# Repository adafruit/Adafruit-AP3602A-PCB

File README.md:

## Adafruit MiniBoost 5V @ 100mA Charge Pump - AP3602A PCB

<a href="http://www.adafruit.com/products/3661"><br/>
Click here to purchase one from the Adafruit shop</a>

PCB files for the Adafruit MiniBoost 5V @ 100mA Charge Pump - AP3602A.

Format is EagleCAD schematic and board layout
* https://www.adafruit.com/product/3661

### Description

This adorable little board will come in very handy whenever you need a small amount of 5V power. It's the size of a linear regulator, but it's actually a mini-booster! Input 3V on one side, and get 5V at up to 100mA supply on the other. Perfect for use with battery-powered projects with 2 or 3 Alkaline, or a single Lithium battery. For big projects, you may want one of our PowerBoost boards that can give you a honkin' 500mA-2A of current.

This booster uses a charge-pump topology, which makes it very compact and low cost. But it isn't as efficient as a inductor-based boost converter. Charge-pumps always double the incoming voltage, and then regulate down. So yeah, not as efficient. So ideal for when you aren't counting coulombs - or when your current draw isn't terribly high.

You get one fully assembled breakout with an AP3602A and components, and a small bit of header. Give 3-5VDC on the IN and ground pins. Then you'll have 5V on the OUT pin. The enable pin can be pulled low to disable the output.

### License

Adafruit invests time and resources providing this open source design, please support Adafruit and open-source hardware by purchasing products from [Adafruit](https://www.adafruit.com)!

Designed by Limor Fried/Ladyada for Adafruit Industries.

Creative Commons Attribution/Share-Alike, all text above must be included in any redistribution.
See license.txt for additional details.

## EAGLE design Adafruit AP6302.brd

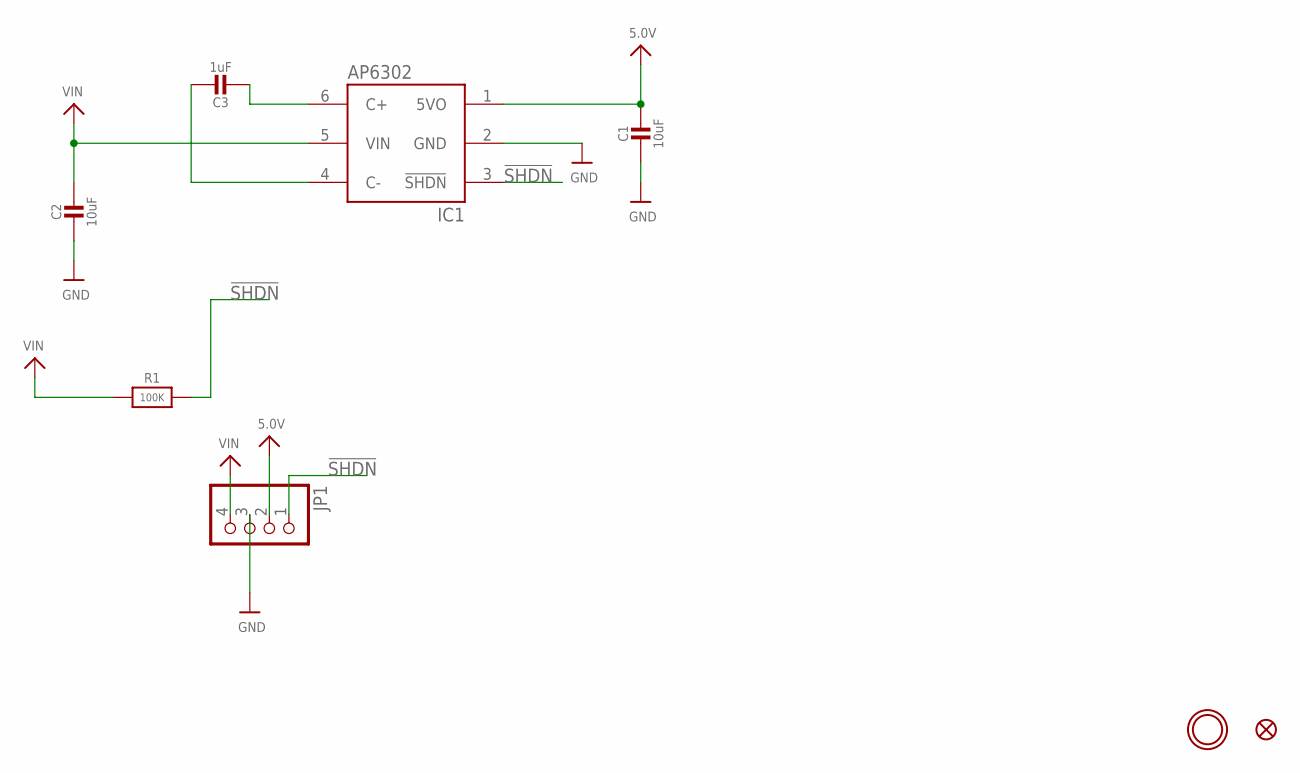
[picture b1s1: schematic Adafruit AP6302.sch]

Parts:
C1, C2: 10uF; 0805-NO
C3: 1uF; 0805-NO
FID1: FIDUCIAL""; FIDUCIAL_1MM
IC1: AP3602; SOT23-6
JP1: HEADER-1X4ROUND; 1X04_ROUND
R1: 100K; 0805-NO
U$9: MOUNTINGHOLE2.5; MOUNTINGHOLE_2.5_PLATED

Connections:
5.0V: C1.1, IC1.1 (5VO), JP1.2
!SHDN: IC1.3 (!SHDN), JP1.1, R1.2
GND: C1.2, C2.2, IC1.2 (GND), JP1.3
unnamed: C3.2, IC1.6 (C+)
unnamed: C3.1, IC1.4 (C-)
VIN: C2.1, IC1.5 (VIN), JP1.4, R1.1

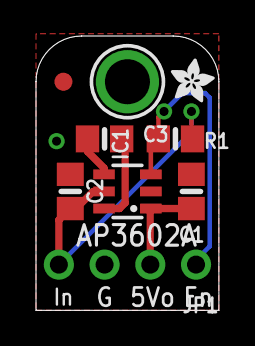
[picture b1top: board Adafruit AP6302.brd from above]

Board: 2 copper layers, 10.2 x 15.2 mm, 10 parts (1 on the bottom side), 6 nets.

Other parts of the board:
U$10: PCBFEAT-REV-040
U$11: ADAFRUIT_2.5MM

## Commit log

2020-06-17 Add board files.

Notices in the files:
parts and their libraries:
microbuilder: This work is placed in the public domain, and may be freely used for commercial and non-commercial work with the following conditions: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
